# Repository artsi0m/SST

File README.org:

* SST — monorepo for pcb, coursework and bachelor thesis

«Система автоматического управления беспилотным летательным аппаратом
мультироторного типа»

Ссылка на оригинальную статью и схему:
https://www.elektormagazine.com/labs/super-servo-tester

** file structure
| [[file:README.org]]                                 | Этот файл                                                                     |
| [[file:project-todo.org]]                           | Подсчёт времени и учёт задач в org-mode                                       |
| [[file:calculations/]]                              | Расчёты в org-mode                                                            |
| [[file:calculations/mass.org]]                      | Расчёт массы ПП                                                               |
| [[file:calculations/hole_unification.org]]          | Подсчёт количества однотипных отверстий для чертежа ПП                        |
| [[file:pcb/]]                                       | Плата из KiCAD, топология и схема Э3 и Э1                                     |
| [[file:pcb/3dmodels]]                               | 3D модели в формате STEP для моделирования в CAE                              |
| [[file:pcb/plots]]                                  | Слои печатной платы в dxf для чертежа печатной платы и сборочного в dwg       |
| [[file:pcb/build]]                                  | Производственные файлы и 3D модели платы                                      |
| [[file:pcb/build/sst-kicad-export5.step]]           | Экспортированная из KiCAD в формате step 3D модель печатной платы             |
| [[file:pcb/build/sst-freecad-export6.step]]         | Упрощенная во FreeCAD 3D модель печатйно платы в формате STEP и без отверстий |
| [[file:bachelor-thesis/]]                           | Пояснительная записка дипломной работы                                        |
| [[file:bachelor-thesis/KarakinBachelorThesis.bib]]  | Библиография дипломной работы                                                 |
| [[file:bachelor-thesis/main.tex]]                   | Входная точка для сборки пояснительной записки                                |
| [[file:bachelor-thesis/bsuir-std.cls]]              | Латех класс для соответствия стандарту СТП                                    |
| [[file:sel/]]                                       | Перечень элементов, ПЭ3                                                       |
| [[file:sel/xesel.cls]]                              | Чужой латех класс для перечня элементов                                       |
| [[file:terms-of-reference/]]                        | Техническое Задание                                                           |
| [[file:project-proposal/]]                          | План проспект                                                                 |
| [[file:coursework-paper/]]                          | Пояснительная записка курсовой работы                                         |
| [[file:coursework-paper/Karakin7semCoursework.bib]] | Библиография курсовой работы                                                  |
| [[file:coursework-paper/main.tex]]                  | Входная точка для сборки пояснительной записки (курсовой)                     |

** dependencies

https://github.com/artsi0m/kicad-symbols-gost/tree/artsi0m-kicad-v8

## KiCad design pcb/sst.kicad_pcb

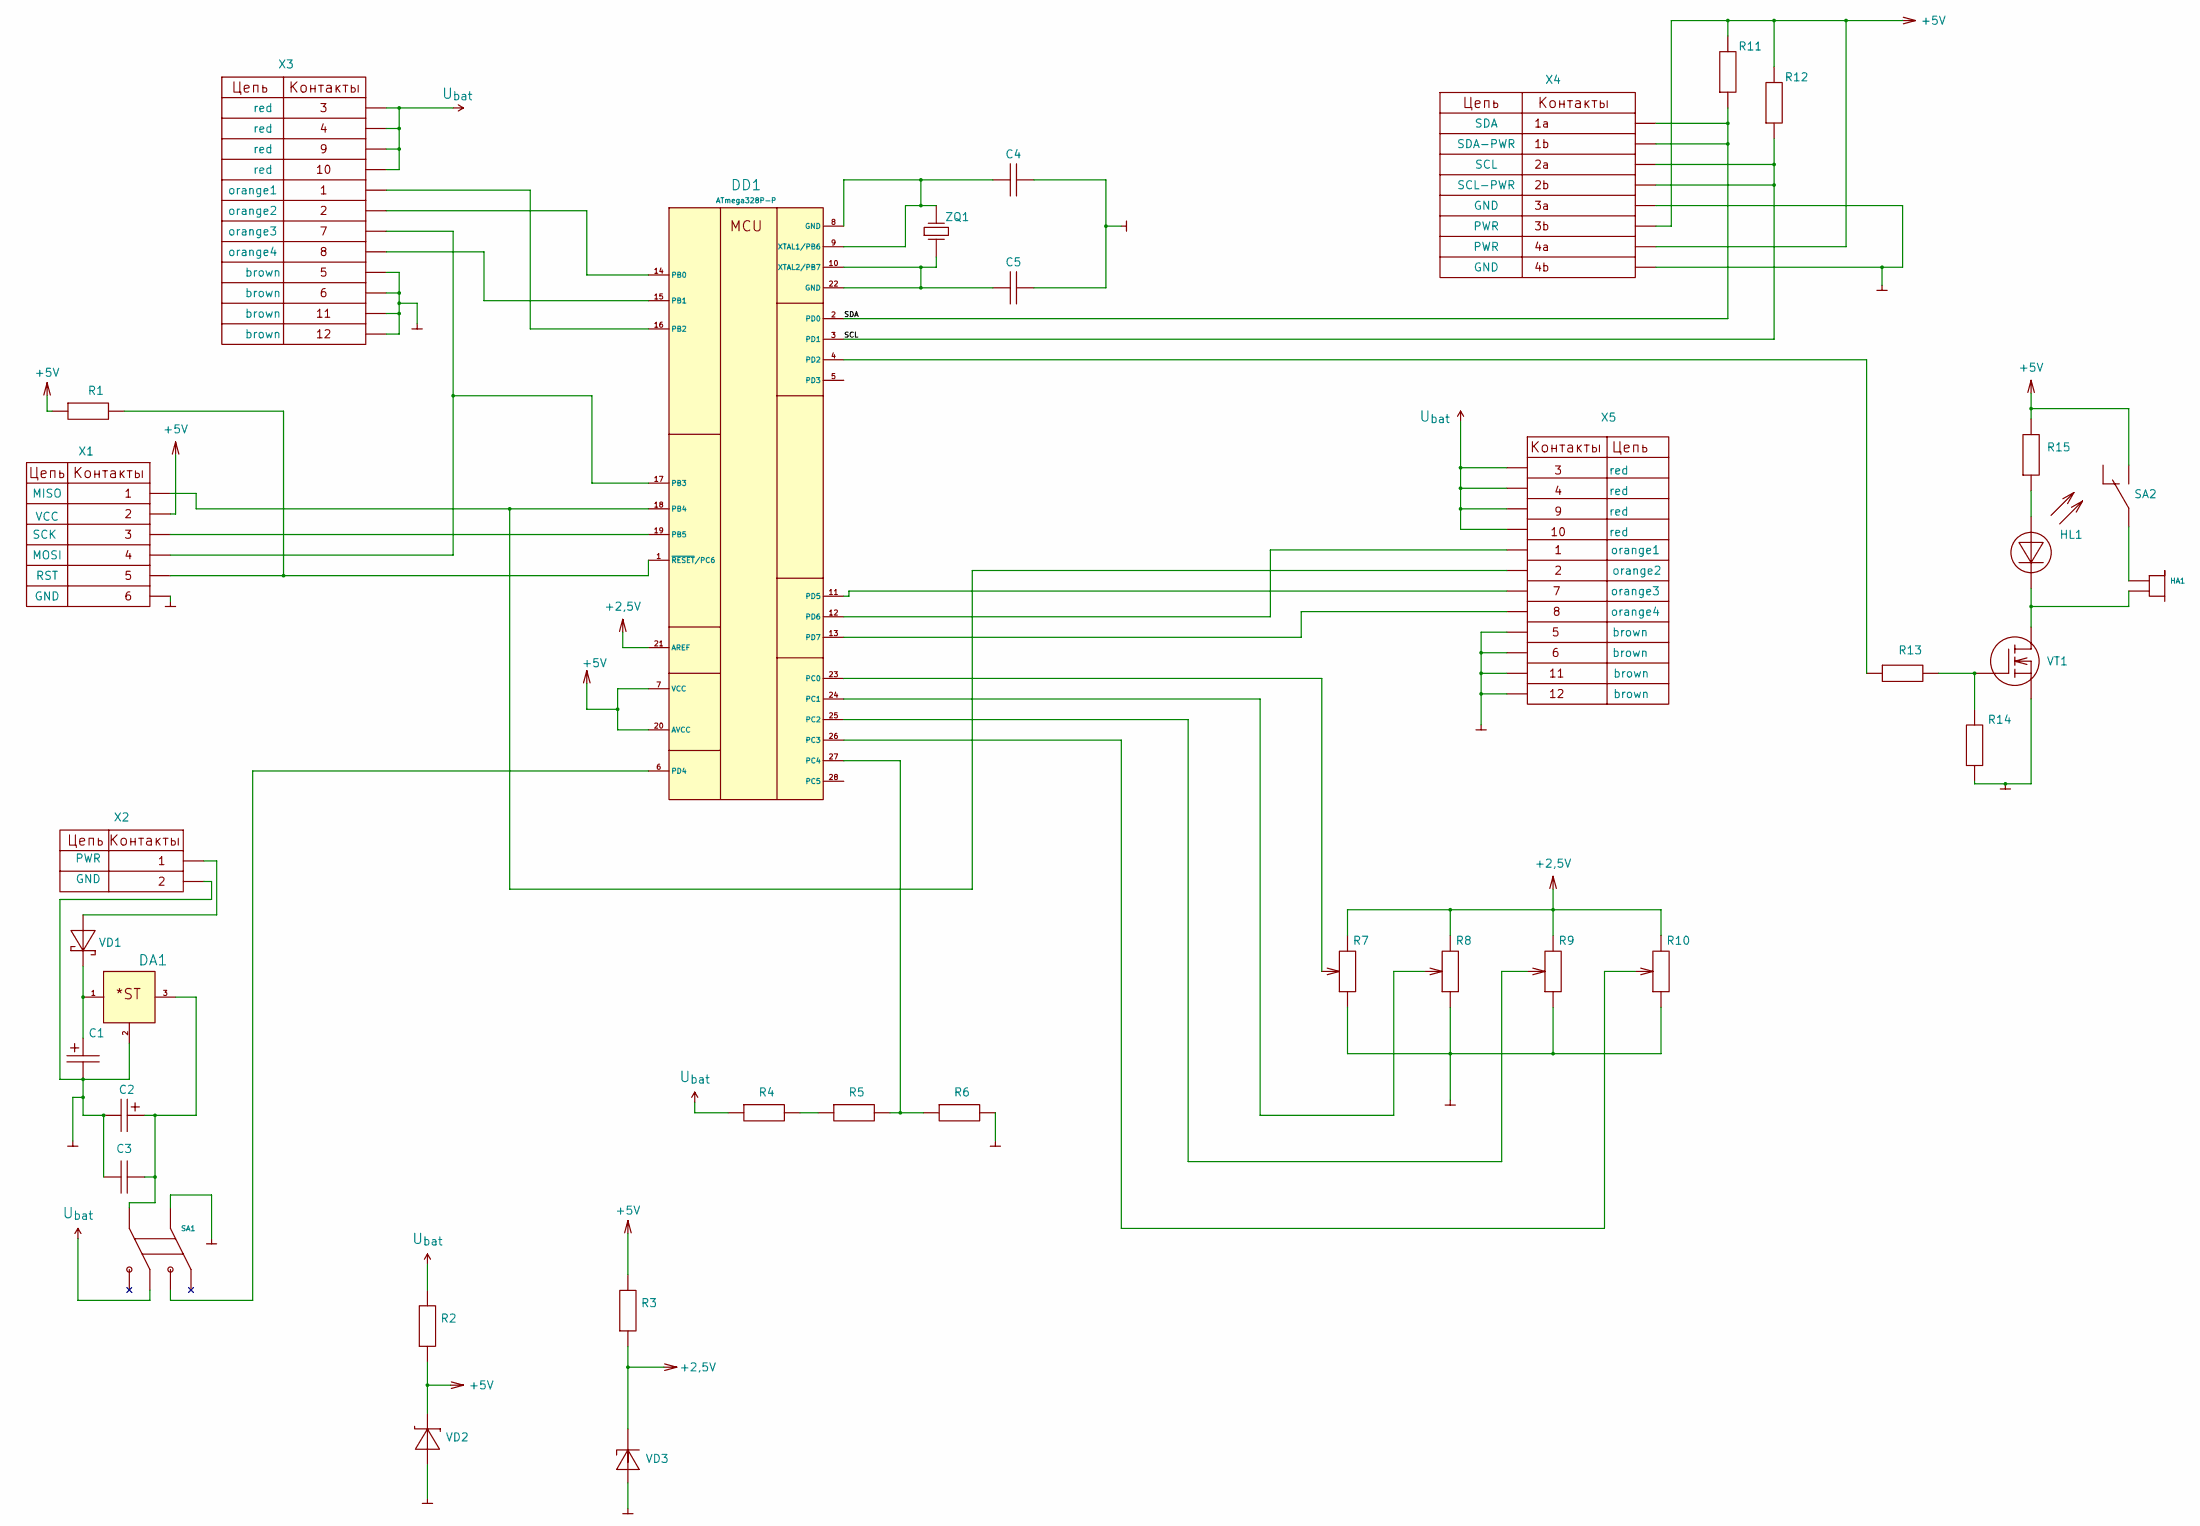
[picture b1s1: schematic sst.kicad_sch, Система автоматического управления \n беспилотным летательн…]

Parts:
C1: 100мк; CP_Radial_D13.0mm_P5.00mm
C2: 10мк 16В; CP_Radial_D13.0mm_P5.00mm
C3: 100н; C_Disc_D7.5mm_W5.0mm_P5.00mm
C4, C5: 22п; C_0805_2012Metric_Pad1.18x1.45mm_HandSolder
DA1: LM7805_TO220; TO-220-3_Vertical
DD1: ATmega328P-P; DIP-28_W7.62mm
HA1: Buzzer; Buzzer_15x7.5RM7.6
HL1: HL_LED; LED_D3.0mm
R1, R4, R5, R6, R11, R12, R14: 10к 0,25Вт; R_Axial_DIN0207_L6.3mm_D2.5mm_P7.62mm_Horizontal
R2, R13: 22 0,25Вт; R_Axial_DIN0204_L3.6mm_D1.6mm_P5.08mm_Horizontal
R3, R15: 1к 0,25Вт; R_Axial_DIN0207_L6.3mm_D2.5mm_P7.62mm_Horizontal
R7, R8, R9, R10: потенциометр 10к 0,25Вт; Potentiometer_TT_P0915N
SA1: SA_DPDT; SW_CK_JS202011AQN_DPDT_Angled
SA2: SA_SPDT; SW_Slide_SPDT_Angled_CK_OS102011MA1Q
VD1: 1N5817 шотки; D_DO-41_SOD81_P7.62mm_Horizontal
VD2: 5,1В шотки; D_DO-35_SOD27_P7.62mm_Horizontal
VD3: LM385BZ-2.5; TO-92_Inline
VT1: 2N7000; TO-92
X1: CONN_SPI; PinHeader_2x03_P1.00mm_Horizontal
X2: CONN_PWR; BarrelJack_Kycon_KLDX-0202-xC_Horizontal
X3, X5: CONN_INPUTS; PinHeader_2x06_P2.54mm_Horizontal
X4: CONN_I2C; PinSocket_2x04_P1.27mm_Vertical
ZQ1: 1М; Crystal_HC49-U_Vertical

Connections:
+2,5V: DD1.21 (AREF), R3.1, R7.3, R8.3, R9.3, R10.3, VD3.1 (K)
+5V: DD1.7 (VCC), DD1.20 (AVCC), R1.1, R2.1, R3.2, R11.2, R12.2, R15.2, SA2.2, VD2.1 (K), X1.2, X4.6, X4.7
/SCL: DD1.3 (PD1), R12.1, X4.3, X4.4
/SDA: DD1.2 (PD0), R11.1, X4.1, X4.2
GND: C1.2, C2.2, C3.2, C4.2, C5.1, DA1.2, R6.2, R7.1, R8.1, R9.1, R10.1, R14.1, SA1.1, VD2.2 (A), VD3.2 (A), VT1.1 (S1), X1.6, X2.2, X3.9, X3.10, X3.11, X3.12, X4.5, X4.8, X5.9, X5.10, X5.11, X5.12
unnamed: C2.1, C3.1, DA1.3, SA1.2
unnamed: DD1.14 (PB0), X3.6
unnamed: DD1.15 (PB1), X3.8
unnamed: DD1.16 (PB2), X3.5
unnamed: DD1.17 (PB3), X1.4, X3.7
unnamed: DD1.18 (PB4), X1.1, X5.6
unnamed: DD1.19 (PB5), X1.3
unnamed: DD1.23 (PC0), R7.2
unnamed: DD1.24 (PC1), R8.2
unnamed: DD1.25 (PC2), R9.2
unnamed: DD1.26 (PC3), R10.2
unnamed: DD1.27 (PC4), R5.2, R6.1
unnamed: DD1.4 (PD2), R13.1
unnamed: DD1.6 (PD4), SA1.3
unnamed: DD1.11 (PD5), X5.7
unnamed: DD1.12 (PD6), X5.5
unnamed: DD1.13 (PD7), X5.8
unnamed: C4.1, DD1.8 (GND), DD1.9 (XTAL1/PB6), ZQ1.2
unnamed: C5.2, DD1.10 (XTAL2/PB7), DD1.22 (GND), ZQ1.1
unnamed: DD1.1 (~RESET/PC6), R1.2, X1.5
unnamed: HA1.1 (+), SA2.1
unnamed: HA1.2 (-), HL1.1 (K), VT1.3 (D1)
unnamed: HL1.2 (A), R15.1
unnamed: R4.2, R5.1
unnamed: VD1.2 (A), X2.1
unnamed: C1.1, DA1.1, VD1.1 (K)
unnamed: R13.2, R14.2, VT1.2 (G1)
U_{bat}: R2.2, R4.1, SA1.5, X3.1, X3.2, X3.3, X3.4, X5.1, X5.2, X5.3, X5.4

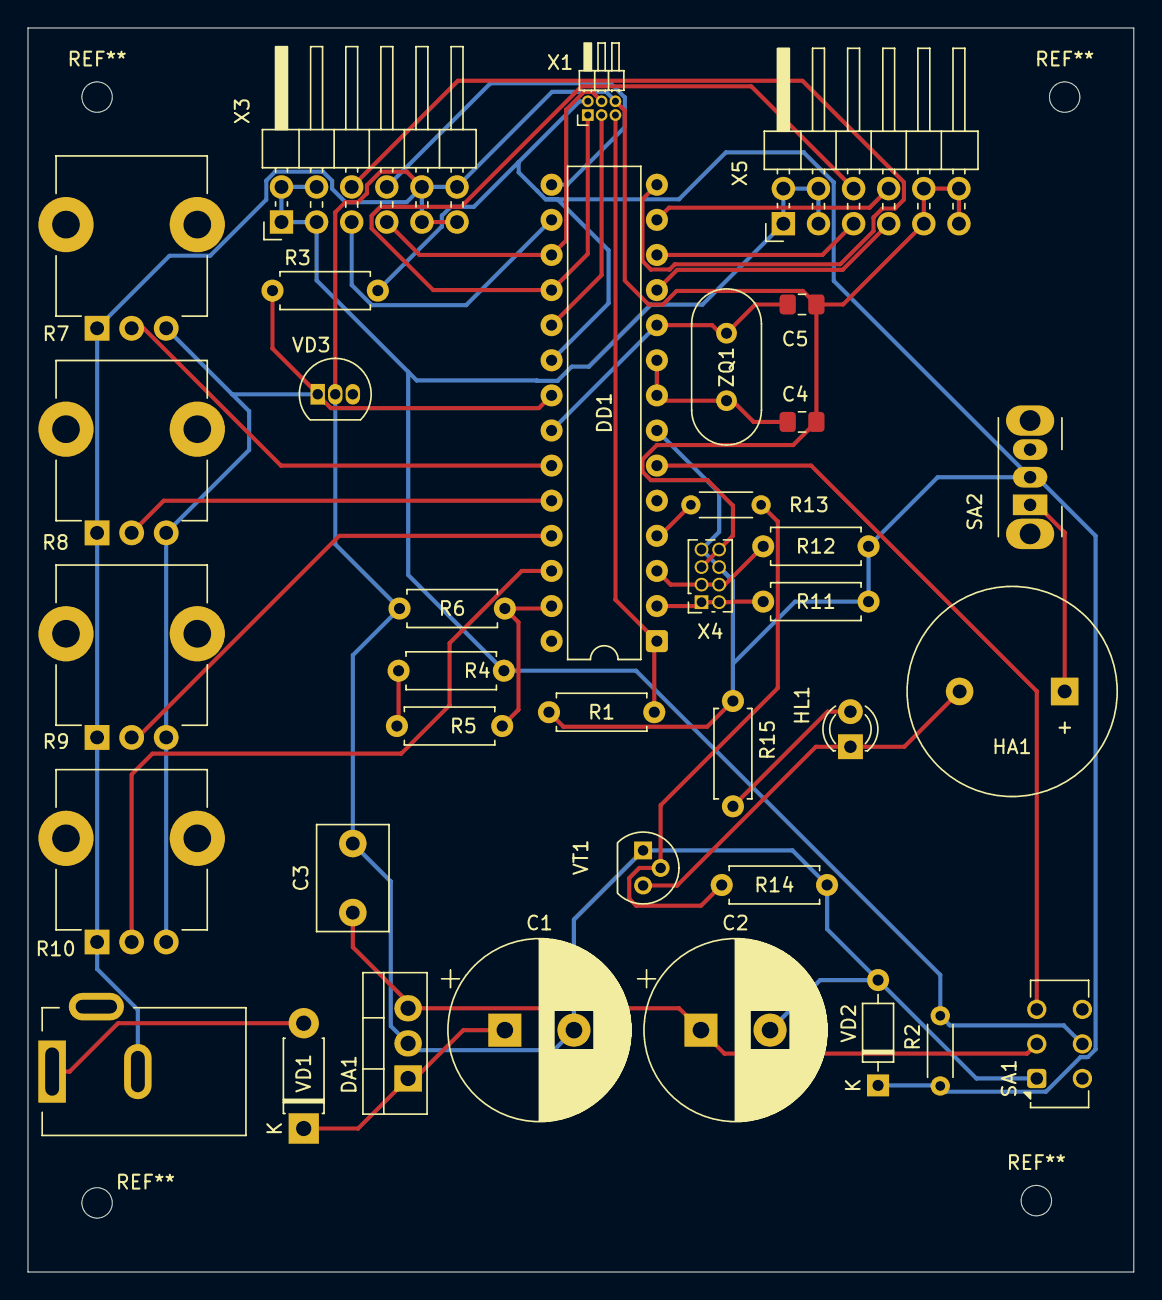
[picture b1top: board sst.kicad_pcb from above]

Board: 2 copper layers, 80.0 x 90.0 mm, 36 parts (0 on the bottom side), 33 nets.

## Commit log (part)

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2024-10-27 Резистор, символ заземления, подписаны цепи, библиотека для струкурной схемы.
2024-10-28 проект структурной схемы
2024-10-28 рамка для структурной схемы
2024-10-28 started writing coursework
2024-10-29 трассировка печатной платы
2024-10-29 Трассировка печатной платы. Файл с трассировкой
2024-10-30 списки больше соотвествуют СТП
2024-11-12 значения комопнентов на Э3 для эксперементов с генерацией ПЭ3
2024-11-12 переместил компонент разъёма для ШИМ
2024-11-12 Попытки написать перечень в xelatex
2024-11-12 Перенёс техническое задание из репозитория с лабами
2024-11-21 Нумерация формул в соответствии с разделами
2024-11-22 Правильная нумерация и подписи к рисункам
2024-11-26 Идентация пунктов в перечислениях в курсовом
2024-11-26 Патентный поиск
2024-11-26 quickfix точки
2024-11-28 moved board and set grid origin
2024-11-30 changed geometry, so the demensions would be 80
2024-12-02 Оформление перечня элементов
2024-12-02 поменял значения на принципиальной схеме
2024-12-02 список использованных источников
2024-12-02 Почти вся третья глава
2024-12-02 Рисунки из патентов
2024-12-06 Надпись электролитический вместо радиальный в перечне
2024-12-09 Подчекрнутые названия компонентов и пустые строки
2024-12-10 Изменения размера символов с схемной библиотеке
2024-12-10 Изменения по замечаниям с пары
2024-12-11 Дописал третью главу
2024-12-12 testing file links in readme
2024-12-12 Локальные переменные и начало написания четвёртой главы
2024-12-12 Попроавки в Э3, другой символ батареи
2024-12-15 Книга из которой берутся расчеты для части 4.1
2024-12-15 Уточнения перечня, добавил изготовителей
2024-12-15 посчитал площади ИЭТ
2024-12-15 Площадь ИЭТ и площадь платы
2024-12-15 приблизительная площадь печатной платы
2024-12-15 Визуально поправляю перечень
2024-12-15 Дописал 4.2
2024-12-15 Добавил транзистор
2024-12-16 Всё что успел на [2024-12-16 15:29]
2024-12-16 Таблица скопированная из перечня элементов
2024-12-16 Больше аббревиатур, встречающихся в тексте.
2024-12-16 Обновил таблицу в соответствие с перечнем
2024-12-16 lambda_e for resistors
2024-12-16 Начал написание пятой главы
2024-12-19 код для вертикальных таблиц
2024-12-19 В содержании названия автоматически в нужный регистр не переходят
2024-12-19 rarely used makefile
2024-12-23 Удаление абзацев после формул и дописывание четвёртой главы
2024-12-23 расчет надёжности
2024-12-24 [2024-12-24 15:48] coursework for this day
2024-12-29 CERN Open Hardware permissive licence
2025-03-11 started translating article with org mode
2025-03-11 написал про режимы работы
2025-03-11 Написал про аналоговые входы
2025-03-11 написал раздел прочее статьи
2025-03-11 дописал весь текст статьи и прогнал spellcheck
2025-03-19 Обновил TODO
2025-03-19 схема на A2, девятая версия KiCAD
2025-03-19 Дедлайны в TODO проекта
2025-03-23 Доработка структурной схемы
2025-03-25 доработка перечня элементов
2025-03-25 Изменения в старом ТЗ
2025-03-25 нужно будет написать новое ТЗ.
2025-03-25 использую класс для ТЗ в план проспекте
2025-03-25 Использую в план проспекте библиографию из курсового
2025-03-25 План проспект
2025-03-26 Новое ТЗ
2025-03-27 Начало написания пояснительной записки для диплома
2025-03-27 Перенос актуального текста из пояснительной записки к курсовому
2025-04-27 переаннотировал схему
2025-04-27 todo по всем недочётам с первой опроцентовки и todo ко второй
2025-05-02 скопировал расчёт надёжности
2025-05-02 +todo
2025-05-02 децимальный номер на принципиальной схеме
2025-05-02 [2025-05-02 17:21]: todo update
2025-05-04 [2025-05-04 19:06] todo update
2025-05-06 меняю заголовок, чтобы написать технико экономическое обоснование
2025-05-06 [2025-05-06 15:21] todo
2025-05-08 каталог с расчётами в орг таблицах, экономического обоснования расчёт
2025-05-08 экономика, что нужно сделать перед расчётом
2025-05-08 доработка принципиальной схемы: VD3 без ворнинга
2025-05-08 перешёл на девятую версию KiCAD
2025-05-08 Обозначение питания как +2,5V, а не 2V5
2025-05-08 заполнил новый перечень резисторами
2025-05-08 Заполнил перечень элементов
2025-05-08 перечень в текстовом виде
2025-05-08 fix заголовка
2025-05-08 [2025-05-08 20:58] todo
2025-05-09 выполняя расчёт экономики, обнаружил неточности в перечне
2025-05-09 перечень элементов, объеденил компоненты
2025-05-10 расчёт стоимости резисторов в экономическом обосновании
2025-05-10 посчитал все резисторы для экономического обоснования
2025-05-10 экономическое обоснование: зуммеры и светодиоды
2025-05-10 экономическое обосноавние: перключатели, диоды, резонатор кварцевый
2025-05-10 другой разъём питания
2025-05-11 экономический расчёт: материалы и комплектующие
2025-05-11 экономический расчёт: отпускная цена изделия
2025-05-11 экономическое обоснование: инвестиции и ROI
2025-05-11 fix spelling in bibliography
2025-05-12 перечень в формате орг
2025-05-12 установил solidworks
2025-05-12 расчёт надёжности: поменял тип пайки
2025-05-13 расчёт по надёжности: выбор математических моделей (частично)
2025-05-13 экономическое обоснование: таблицы с материалами и компонентами
2025-05-13 fix spelling
2025-05-13 Расчёт экономики: внес заклепки как компонент
2025-05-13 методичка по экономике как новый источник
2025-05-13 [2025-05-13 20:57] todo; поставил ANSYS, доделываю расчёт экономики
2025-05-13 экономическое обоснование: таблица отпускной цены с формулами
2025-05-13 экономическое обосноваени: всё что пока есть
2025-05-14 расчёт экономики инвестиции в разработку
2025-05-14 экономическое обосноание: перенёс расчёт в диплом
2025-05-15 новые каталоги в README
2025-05-15 ссылки в README
2025-05-16 расчёт экономики: описание устройства
2025-05-16 экономическое обоснование/spellcheck
2025-05-16 only formulas in production cost table
2025-05-16 экономическое обоснование: отпускная цена и материалы
2025-05-16 экономическое обоснование: расчёт чистой прибыли
2025-05-16 экономическое обоснование: почти что всё
2025-05-16 important note
2025-05-16 Экономическое обосноание: перерасчёт ROI
2025-05-17 экономическое обоснование: опечатки и таблица с зарплатой
2025-05-17 расчёт надёжности: мат модели, интегральные схемы
2025-05-17 трассировка: два слоя, но без переходных отверстий
2025-05-18 script that lists footprints ids
2025-05-18 .gitignore for python
2025-05-20 экономическое обоснование: исправление ошибок
2025-05-20 установил autocad, немного перетащил шелкографию
2025-05-20 экономическое обосноавние: зарплата техника проектировщика
2025-05-21 экономическое обоснование/финальное исправление недочётов
2025-05-21 [2025-05-21 22:39]
2025-05-23 spelling, link to dependency
2025-05-23 убираю предупреждения
2025-05-23 [2025-05-23 22:49]
2025-05-23 обновлённый перечень
2025-05-24 fetch new version
2025-05-24 separate pages
2025-05-24 пустая строка в конце и в начале страницы
2025-05-24 Вписывание названия
2025-05-25 структурированный туду, новые папки в ридми
2025-05-25 mounting holes, grid origin, drill origin
2025-05-25 [2025-05-25 22:16] сократил TODO
2025-05-25 Перенос страниц в перечне элементов
2025-05-26 экспорт печатной платы в dxf
2025-05-26 размер платы 80x90mm
2025-05-26 80x90mm
2025-05-26 - ещё один проводник с углом под 90 градусов
2025-05-26 grid origin on the bottom left corner of the board
2025-05-26 Внешние датчики с большой буквы. Надо доделать рамку
2025-05-26 выполнение чертежа платы
2025-05-27 шрифт OpenGost Type A italic везде на форматной рамке
2025-05-27 не хранить форматную рамку вместе с чертежем
2025-05-28 исправлние УГО: DA1, SA1, VD3
2025-05-28 выполнение чертежа печатной платы
2025-05-29 mass of the PCB
2025-05-30 кондесатор такого номинала не может быть радиальным
2025-05-30 экспорт dxf для сборочного.
2025-05-30 отверстия из чертежа платы
2025-05-30 СФ2-1,5-35 в качестве материала
2025-05-30 [2025-05-30 18:40] три дня чистого времени, как делаю диплом
2025-06-01 [2025-06-01 22:30] моделирование
2025-06-02 добавил рецензента и организацию
2025-06-02 название по приказу
2025-06-02 [2025-06-02 22:01]
2025-06-03 упрощенная модель микросхемы
2025-06-03 do not scale models
2025-06-03 simplify 2x03 pin header
2025-06-03 Simplifed CP_Radial_D13.0mm
2025-06-03 .step instead of .wrl everywhere on the board
2025-06-03 simplify C_Radial_D10.0mm and SA2
2025-06-03 [2025-06-03 13:40]
2025-06-03 simplified PinSocket
2025-06-03 simplified Crystal
2025-06-03 simplified VD1
2025-06-03 simplified DA1
2025-06-03 упростил R DIN0204
2025-06-03 simplified R DIN0207
2025-06-03 export in proper file
2025-06-04 simplified VD3
2025-06-04 R DIN 0204 as a Cubes
2025-06-04 simplified buzzer
2025-06-04 simplifed Buzzer and VT1
2025-06-04 DIN0207 resistors on the right place
2025-06-04 VD2 as a Cube
2025-06-04 added Cube for KLDX0202 connector
2025-06-04 [2025-06-04 17:18]
2025-06-04 .step of PCB for modeling
2025-06-05 STEP file almost without holes on PCB
2025-06-05 [2025-06-05 16:00] LF line endings
2025-06-05 started writing project spec
2025-06-05 LF line endings
2025-06-05 quick fix
2025-06-05 наклон у шрифта
2025-06-05 Практически полная спецификация + правильный децимальный номер
2025-06-06 полная спецификация на проект
2025-06-06 Лишние абазацы; все подразделы записки
2025-06-06 начал писать спецификацию печатной платы
2025-06-07 внёс недостающие главы
2025-06-07 [2025-06-07 17:35]
2025-06-07 формулы к расчёту электрических параметров и режимов работы каскадов
2025-06-07 картинки к патентам
2025-06-09 третий, частично четвёртый патенты
2025-06-09 chapter-1 spell check
2025-06-09 четвёртвый патент
2025-06-09 рисунки для патентного поиска, патент CN113341830A
2025-06-09 LF line endings, clickable links in TOC
2025-06-09 Пятый патент
2025-06-09 введение в расчёт механики платы
2025-06-09 расчёт массы ПП вместе с ЭРЭ
2025-06-09 опечатка в ссылке
2025-06-09 встреча в zoom на тему защиты диплома
2025-06-10 [2025-06-10 10:52]
2025-06-10 спецификация в eskdx
2025-06-10 обеспечение требований стандартизации
2025-06-11 use biber for bibliography
2025-06-11 [2025-06-11 10:42]
2025-06-11 Доработка спецификаций (2)
2025-06-11 upright math font
2025-06-11 keep non-cyrillic words upright, remove \textit{}
2025-06-11 требования нормоконтроля к кеглю заголовков
2025-06-11 [2025-06-11 22:49]
2025-06-12 картинки из учебника Роткопа
2025-06-12 условная поверхность нагретой зоны
2025-06-12 удельная мощность нагретой зоны
2025-06-12 theta 1
2025-06-12 Рисунок 4.4 из Rotkop1976
2025-06-12 коэффициент theta2
2025-06-12 Расчёт теплового режима
2025-06-12 \sloppy command, import from xelatex-bsuir-std
2025-06-12 другой список, другие кавычки
2025-06-12 настройки страницы из xelatex-bsuir-std
2025-06-12 нумерация страниц, настройка формул на русском в нужном месте
2025-06-12 таблица с характеристиками стеклотекстолита
2025-06-12 импорт настроек таблицы из xelatex-bsuir-std
2025-06-12 реферат и введение
2025-06-12 почему-то эта часть с русским в формулах должна быть в конце чтобы работать
2025-06-12 доработка записки
2025-06-12 [2025-06-12 11:27]
2025-06-12 расчёт конструктивно технологических параметров и надёжность
2025-06-13 на скорую руку сделанные расчёты механических нагрузок
2025-06-13 mention Biber and main within auctex local variables
2025-06-13 move out something that I don't get
2025-06-13 сокращённая шестая глава
2025-06-13 [2025-06-13 11:32]
2025-06-13 use longtable for economics components table
2025-06-13 команда для секций, которые есть в содержание но без номеров
    Ещё убрал несовместимую с titlesec комунду
2025-06-13 наполнение и форматирование пятого и шестого разделов
2025-06-13 take together two numberwithin settings
2025-06-13 Список источников в содержании
2025-06-13 minimize picture, so it fit on the page
2025-06-13 [2025-06-13 23:31]
2025-06-14 наполнение первой и второй глав
2025-06-14 Дописывание шестой главы
2025-06-14 заключения и приложения
2025-06-14 [2025-06-14 15:10]
2025-06-14 [2025-06-14 16:37]
2025-06-14 move back to extarticle, page numbers on the right
2025-06-14 абзацы у секций, импорт из xelatex-bsuir-std
2025-06-14 ручное форматирование, масштаб рисунков
2025-06-14 ручное форматирование, raggedright у подписи к таблице
2025-06-14 подпись к таблице сверху
2025-06-14 импорт из xelatex-bsuir-std
2025-06-14 дописал и уменьшил заключание
2025-06-14 таблица в приложение Е с правильной подписью
2025-06-15 Тот же шрифт для ссылок, что и для всего в списке источников
2025-06-15 справка о патентном поиске
2025-06-15 исправления в расчёте собственной частоты
2025-06-16 Дипломный проект, а не дипломная работа. Форматирование реферата
